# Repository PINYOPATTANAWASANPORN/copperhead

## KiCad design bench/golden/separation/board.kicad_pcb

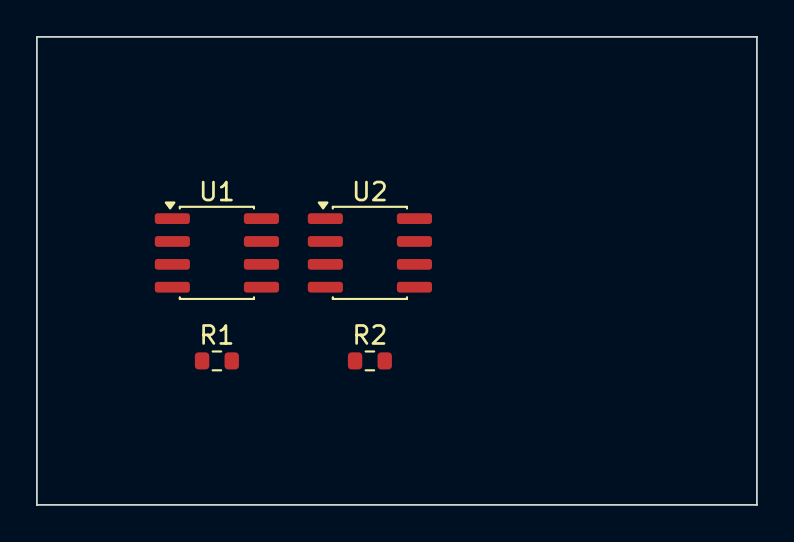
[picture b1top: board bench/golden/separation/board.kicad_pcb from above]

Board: 2 copper layers, 40.0 x 26.0 mm, 4 parts (0 on the bottom side), 4 nets, no tracks yet.

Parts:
R1, R2: 10k; R_0603_1608Metric
U1: OPAMP; SOIC-8_3.9x4.9mm_P1.27mm
U2: MCU; SOIC-8_3.9x4.9mm_P1.27mm

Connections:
AIN: R1.1, U1.1
GND: R1.2, R2.2, U1.4, U2.4
IO: R2.1, U2.5
SIG: U1.6, U2.3

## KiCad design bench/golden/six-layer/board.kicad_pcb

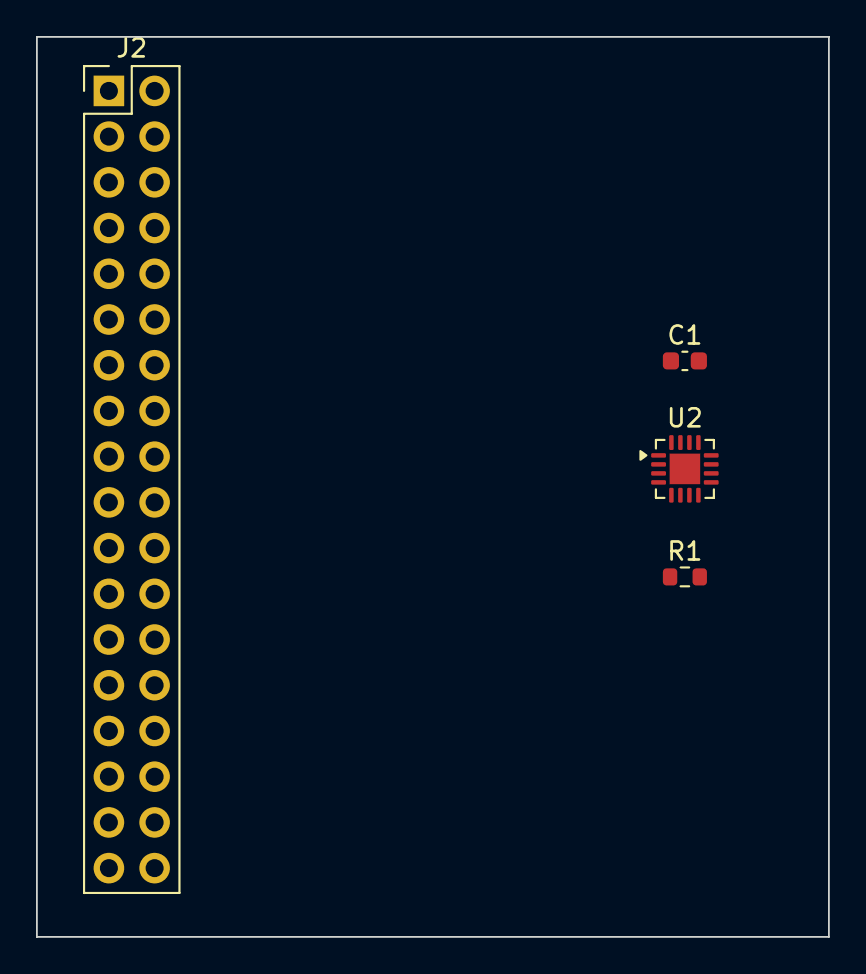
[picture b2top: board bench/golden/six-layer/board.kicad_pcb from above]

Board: 6 copper layers, 44.0 x 50.0 mm, 4 parts (0 on the bottom side), 19 nets, no tracks yet.

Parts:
C1: 100n; C_0603_1608Metric
J2: CONN; PinHeader_2x18_P2.54mm_Vertical
R1: 10k; R_0603_1608Metric
U2: MCU; QFN-16-1EP_3x3mm_P0.5mm_EP1.7x1.7mm

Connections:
GND: C1.2, J2.36, U2.17
PU: J2.34, R1.2
S1: J2.1, U2.1
S2: J2.2, U2.2
S3: J2.3, U2.3
S4: J2.4, U2.4
S5: J2.5, U2.5
S6: J2.6, U2.6
S7: J2.7, U2.7
S8: J2.8, U2.8
S9: J2.9, U2.9
S10: J2.10, U2.10
S11: J2.11, U2.11
S12: J2.12, U2.12
S13: J2.13, U2.13
S14: J2.14, U2.14
S15: J2.15, U2.15
S16: J2.16, U2.16
VCC: C1.1, J2.35, R1.1

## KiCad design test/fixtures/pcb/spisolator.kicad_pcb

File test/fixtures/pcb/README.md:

`spisolator.kicad_pcb` — the `spisolator_spisolator` board from PCBench (github.com/PCBench/PCBench at `dec3be7`, MIT; board license recorded as MIT in the corpus metadata), upgraded with `kicad-cli pcb upgrade --force`. A KiCad 4 board with a back-side SOIC and KiCad 10's name-only net dialect; used to hold the DSN emitter and the kicad-tools dialect rewrite to what KiCad's own exporter produces.

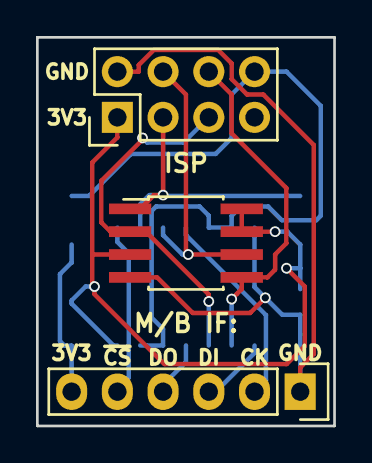
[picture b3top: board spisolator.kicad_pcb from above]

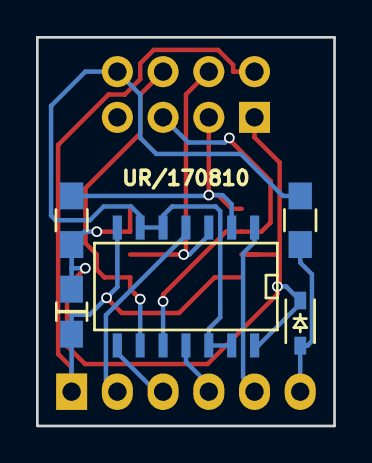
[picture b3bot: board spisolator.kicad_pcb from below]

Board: 2 copper layers, 16.5 x 21.6 mm, 8 parts (5 on the bottom side), 12 nets.

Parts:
C1: 1u; C_0805_HandSoldering
D1: -; SOD-323
P1: CONN_01X06; Socket_Strip_Straight_1x06
P2: CONN_02X04; Pin_Header_Straight_2x04
R1, R2: 4k7; R_0805_HandSoldering
U1: 4066; SOIC-14_N
U2: SPI_TGT; SOIC-8_3.9x4.9mm_Pitch1.27mm

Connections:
+3V3: C1.2, D1.1, P2.1, R2.1, U1.14, U2.3, U2.7, U2.8
/BUFEN: P2.8, R1.1, U1.5, U1.6, U1.12, U1.13
/MB3V3: D1.2, P1.6, R1.2
/MBMISO: P1.4, U1.11
/MBMOSI: P1.3, U1.8
/MBSCK: P1.2, U1.4
/MISO: P2.5, U1.10, U2.2
/MOSI: P2.6, U1.9, U2.5
/SCK: P2.4, U1.3, U2.6
/~CS: P2.3, R2.2, U1.2, U2.1
/~MBCS: P1.5, U1.1
GND: C1.1, P1.1, P2.2, U1.7, U2.4

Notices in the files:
bench/golden/separation/board.kicad_pcb:
copperhead golden microboard; footprints from the KiCad libraries (CC-BY-SA-4.0 with the KiCad library exception)
